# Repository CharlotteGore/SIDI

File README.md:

SIDI
====

This code is to control a SID using the [MOS6581 SID Control Library](https://github.com/CharlotteGore/MOS6581) library, taking MIDI input for frequency control and, currently, a load of analog inputs for everything else.

It also uses the [SIDFreak - MIDI note to SID Frequency lookup](https://github.com/CharlotteGore/SIDFreak) library, which helps translate MIDI notes into the correct SID phase accumulator values to achieve specific frequencies.

##Update

Have added EAGLE files for the board. This is the other half of the board that's in the MOS6581 library. It holds the 1mhz crystal, an ATMega328P, exposes I2C, ICSP and SID_DATA headers and has a MIDI-In on the UART. This needs programming via ICSP, as the RX pin is being used by the MIDI input.

Note that this board is for the future version of SIDI, which uses I2C peripherals for control data... and it's not back from the PCB printers yet so I don't know whether or not it works*. FUN TIMES.

*Actually the version I sent off to the printers don't work. The RESET pin on the ATMega328P is pulled to ground instead of +5v. Whoops. The schematic and board files have been updated in this repo, but it's Manual Bodge time when the boards arrive..

##Progress

Right now I have a basic but working control surface for controlling the SID.

It exposes all the registers, plus a little bit extra (octave shifting, switching between keyboard control and a frequency knob etc). Enough to actually make music on SIDs but not enough to truly bring out the full power of it. A couple of 4051 demux chips, a bunch of pots, some toggle switches with pull-up resistors and a timer interrupt vector to do periodic reading. Classic "My First MIDI Controller" stuff except with some nasty PORT manipulation stuff for fun.

Using standard analog potentiometers has proven to be a bit disappointing though, all in all. Keeping a track of what's what when you switch between the voices is incredibly difficult, jarring jumps etc.. total lack of repeatability of sounds. Hmmm.. is that a bad thing though? Probably is. Yes. 

Toggle switches are a terrible idea for these toggleable values too. They need to be buttons which turn LEDs on and off in order to show the current status properly. Having to flip a toggle twice to turn on something that looks like it should be on is just wrong. Bad UX.

The ideal solution - if potentially expensive and-requiring-SMD-soldering solution - is to switch to rotary encoders with LEDs indicating the current value. This means that when the underlying 'real' value changes, the musician can see where the dials are currently set at a glance. Relative controls!

This makes loading and saving patches something very very practical and intuitive, too. The long term plan of being able to load and save patches from an SD card is something that's always in the back of my mind. It's not enough to simply load the sounds - you want to see how those sounds are put together and tweak them in small ways, not instantly break them with no way of getting them back without reloading the patch.

The problem is that there's only a limited amount of rotary encoders you can realistically manage on a single ATMega328 chip. So, my solution (such as it is) is to basically have more. Lots more. Lots of slave ATMegas on an I2C bus. 

Each ATMega328 can handle either 6-7 Rotary Encoders (or 12-14 push buttons, I think) whilst using the SPI bus to controls LED drivers or shift registers and using the I2C bus to send and recieve current values for controls. 

The advantage of shoving all the controls onto an I2C bus is that the Master only needs know about stuff that's changed (and therefore requires some action to be taken). This liberates the master to devote more clock cycles to manipulating the SID. LFOs, amp envelopes, multiple SIDs for polyphony.. all become more viable. 

I've been doing some proof of concept work today, testing using PIN Change Interrupts for buttons and rotary encoders as well as checking how well the I2C bus performs at the basic 100khz speed and frankly it's more than good enough... and it can go four times faster. 

My next step is to implement my current analog control surface as a standalone I2C module and reprogram this app to use it rather than doing its own reading. This way I can basically swap out the control surface for just about anything, and that's a very good thing.

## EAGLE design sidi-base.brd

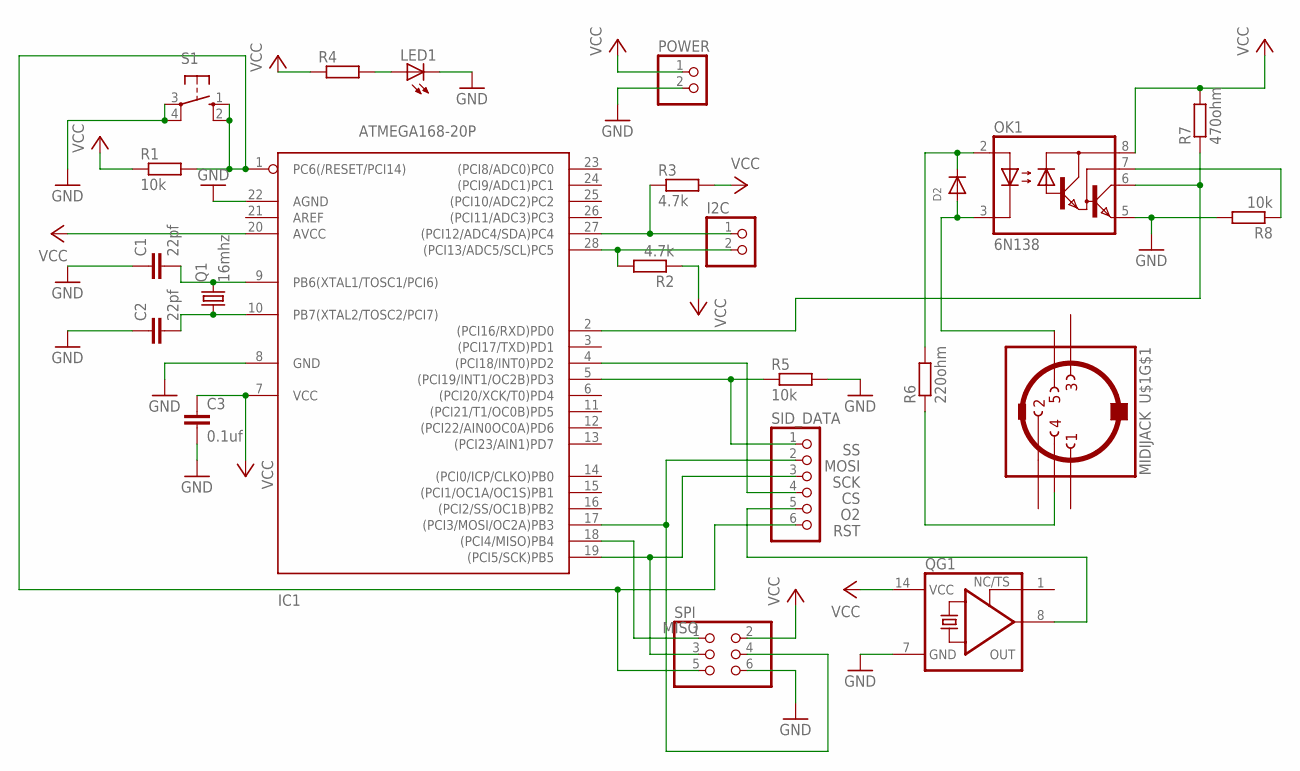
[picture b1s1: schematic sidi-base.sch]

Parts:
C1, C2: 22pf; C050-050X075
C3: 0.1uf; C050-050X075
D2: DIODEDO-1N4148; DO-1N4148
I2C: PINHD-1X2; 1X02
IC1: ATMEGA168-20P; DIL28-3
LED1: LED3MM
OK1: 6N138; DIL08
POWER: PINHD-1X2; 1X02
Q1: 16mhz; HC49/S
QG1: XO-14; DIL14S
R1, R5, R8: 10k; 0207/7
R2, R3: 4.7k; 0207/7
R4: R-EU_0207/7; 0207/7
R6: 220ohm; 0207/7
R7: 470ohm; 0207/7
S1: 10-XX; B3F-10XX
SID_DATA: PINHD-1X6; 1X06
SPI: PINHD-2X3; 2X03
U$1: MIDIJACK; CP-2350

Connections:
CS: IC1.4 ((PCI18/INT0)PD2), SID_DATA.4
GND: C1.1, C2.1, C3.2, IC1.8 (GND), IC1.22 (AGND), LED1.K (C), OK1.5 (GND), POWER.2, QG1.7 (GND), R5.2, R8.2, S1.3, S1.4 (P1), SPI.6
MISO: IC1.18 ((PCI4/MISO)PB4), SPI.1
MOSI: IC1.17 ((PCI3/MOSI/OC2A)PB3), SID_DATA.2, SPI.4
unnamed: OK1.7 (VB), R8.1
unnamed: LED1.A, R4.2
unnamed: C1.2, IC1.9 (PB6(XTAL1/TOSC1/PCI6)), Q1.2
unnamed: C2.2, IC1.10 (PB7(XTAL2/TOSC2/PCI7)), Q1.1
unnamed: I2C.1, IC1.27 ((PCI12/ADC4/SDA)PC4), R3.1
unnamed: I2C.2, IC1.28 ((PCI13/ADC5/SCL)PC5), R2.2
unnamed: D2.A, OK1.3 (C), U$1.5
unnamed: R6.1, U$1.4
unnamed: D2.C, OK1.2 (A), R6.2
unnamed: IC1.2 ((PCI16/RXD)PD0), OK1.6 (VO), R7.1
O2: QG1.8 (OUT), SID_DATA.5
RST: IC1.1 (PC6(/RESET/PCI14)), R1.2, S1.1 (S), S1.2 (S1), SID_DATA.6, SPI.5
SCK: IC1.19 ((PCI5/SCK)PB5), SID_DATA.3, SPI.3
SS: IC1.5 ((PCI19/INT1/OC2B)PD3), R5.1, SID_DATA.1
VCC: C3.1, IC1.7 (VCC), IC1.20 (AVCC), OK1.8 (VCC), POWER.1, QG1.14 (VCC), R1.1, R2.1, R3.2, R4.1, R7.2, SPI.2

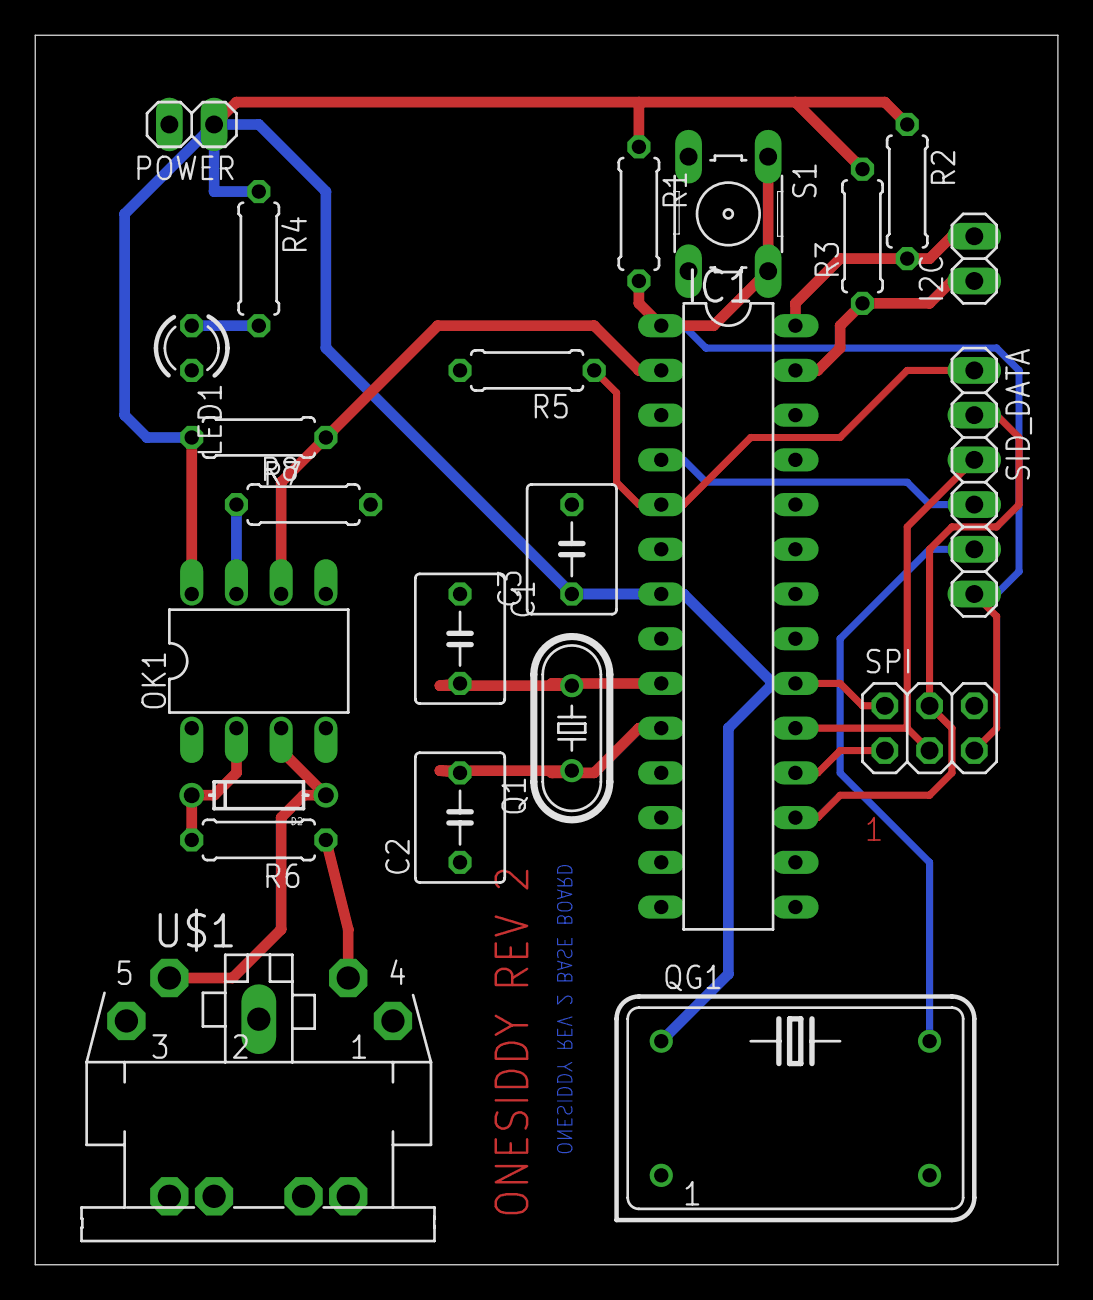
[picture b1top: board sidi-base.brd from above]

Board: 2 copper layers, 58.1 x 69.8 mm, 23 parts (0 on the bottom side), 19 nets.

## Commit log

2013-06-17 Okay.. and now it actually works
2013-06-21 Had to change the order of the inputs (due to new layout). Fixed Octave shifting.
2013-06-30 Added pitch bend. Fixed for compiling in standard ARduino IDE.
2013-06-30 Added some schematics and stuff
2013-07-01 Oops
2013-07-01 Updated schematic
2013-07-14 Latest revision to the board. Control surface code silenced.
